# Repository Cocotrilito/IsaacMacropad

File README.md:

# IsaacMacropad
A highly versatile macropad like a "Swiss-army tool" for my computer workflow usable in many different situations such as video editing, 3d modeling, and general system control The macropad will inclide 3x3 or 2x2 key layout and at least one rotary encoder for precise control. This is my first hardware project, and im really exited about it.

## Project Overview (HackPad)

## Schematic

## PCB Design

## Case Design

## Bom 
| Item | Component | Quantity | Notes |
|-----:|----------|----------|-------|
| 1 | Seeed Studio XIAO RP2040 | 1 | Main microcontroller |
| 2 | Mechanical switches (MX compatible) | 9 | Key switches |
| 3 | Keycaps | 9 | 1u keycaps |
| 4 | EC11 Rotary Encoder | 1 | With push button |
| 5 | OLED Display (128x64 I2C) | 1 | Status display |
| 6 | Diodes 1N4148 | 9 | For key matrix |
| 7 | PCB | 1 | Custom designed |
| 8 | Case | 1 | 3D printed |

##
Thanks for reading if you liked it leave a follow! :)

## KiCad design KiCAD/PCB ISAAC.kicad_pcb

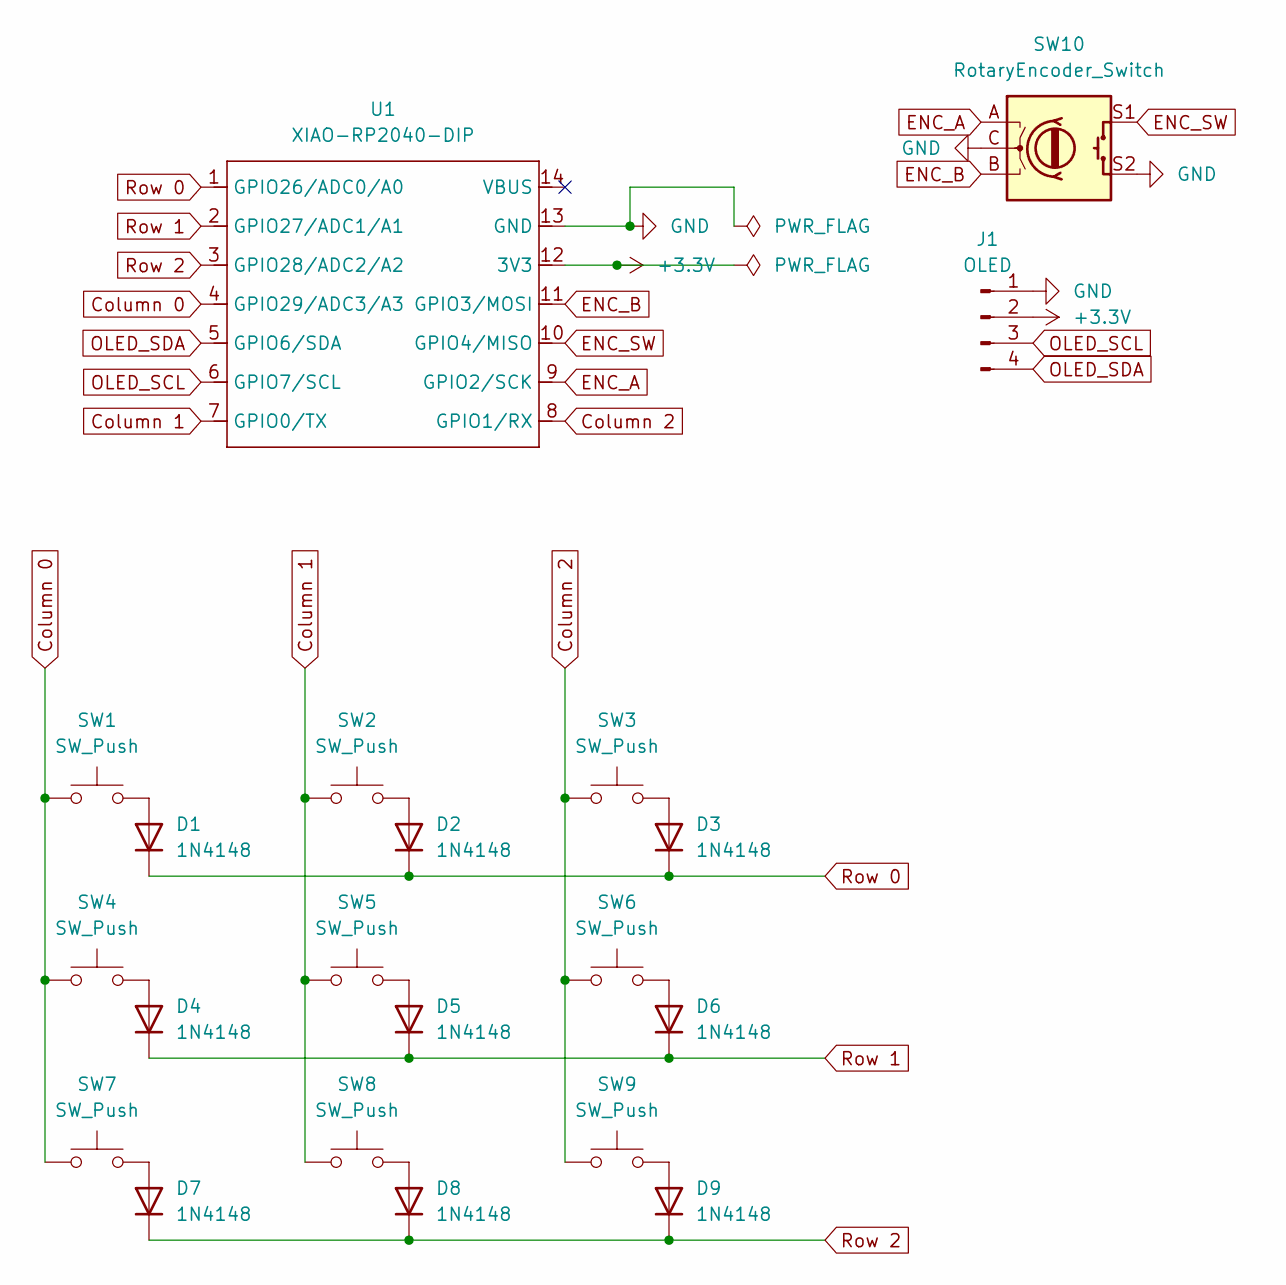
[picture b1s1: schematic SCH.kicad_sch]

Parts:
D1, D2, D3, D4, D5, D6, D7, D8, D9: 1N4148; D_DO-35_SOD27_P7.62mm_Horizontal
J1: OLED; SSD1306-0.91-OLED-4pin-128x32
SW1, SW2, SW3, SW4, SW5, SW6, SW7, SW8, SW9: SW_Push; SW_Cherry_MX_1.00u_PCB
SW10: RotaryEncoder_Switch; RotaryEncoder_Alps_EC11E-Switch_Vertical_H20mm
U1: XIAO-RP2040-DIP

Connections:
+3.3V: J1.2, U1.12 (3V3)
Column 0: SW1.1, SW4.1, SW7.1, U1.4 (GPIO29/ADC3/A3)
Column 1: SW2.1, SW5.1, SW8.1, U1.7 (GPIO0/TX)
Column 2: SW3.1, SW6.1, SW9.1, U1.8 (GPIO1/RX)
ENC_A: SW10.A, U1.9 (GPIO2/SCK)
ENC_B: SW10.B, U1.11 (GPIO3/MOSI)
ENC_SW: SW10.S1, U1.10 (GPIO4/MISO)
GND: J1.1, SW10.C, SW10.S2, U1.13 (GND)
unnamed: D1.2 (A), SW1.2
unnamed: D2.2 (A), SW2.2
unnamed: D3.2 (A), SW3.2
unnamed: D4.2 (A), SW4.2
unnamed: D5.2 (A), SW5.2
unnamed: D6.2 (A), SW6.2
unnamed: D7.2 (A), SW7.2
unnamed: D8.2 (A), SW8.2
unnamed: D9.2 (A), SW9.2
OLED_SCL: J1.3, U1.6 (GPIO7/SCL)
OLED_SDA: J1.4, U1.5 (GPIO6/SDA)
Row 0: D1.1 (K), D2.1 (K), D3.1 (K), U1.1 (GPIO26/ADC0/A0)
Row 1: D4.1 (K), D5.1 (K), D6.1 (K), U1.2 (GPIO27/ADC1/A1)
Row 2: D7.1 (K), D8.1 (K), D9.1 (K), U1.3 (GPIO28/ADC2/A2)

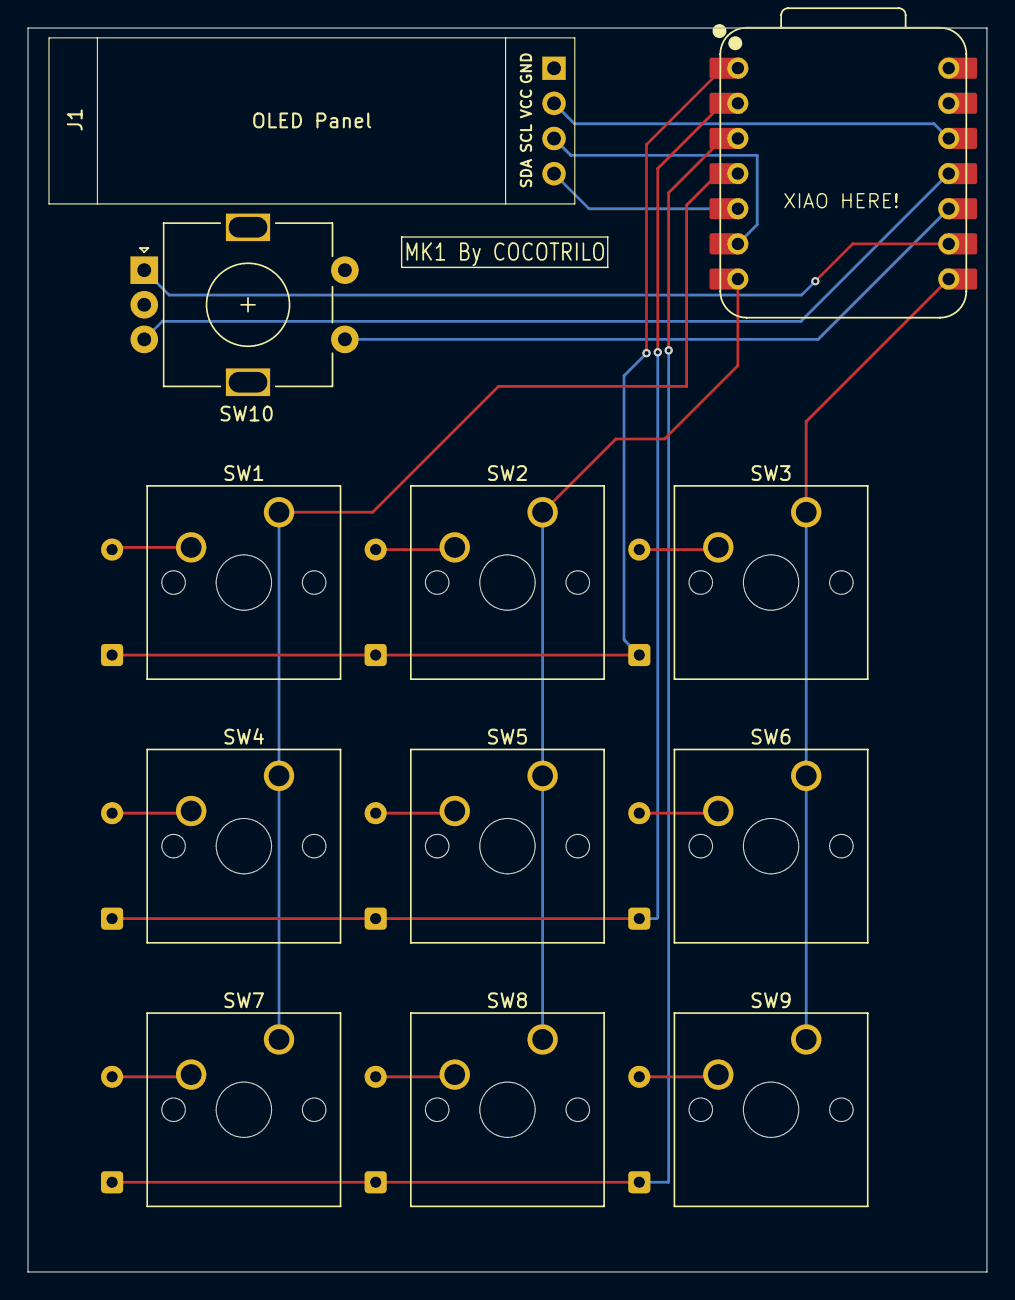
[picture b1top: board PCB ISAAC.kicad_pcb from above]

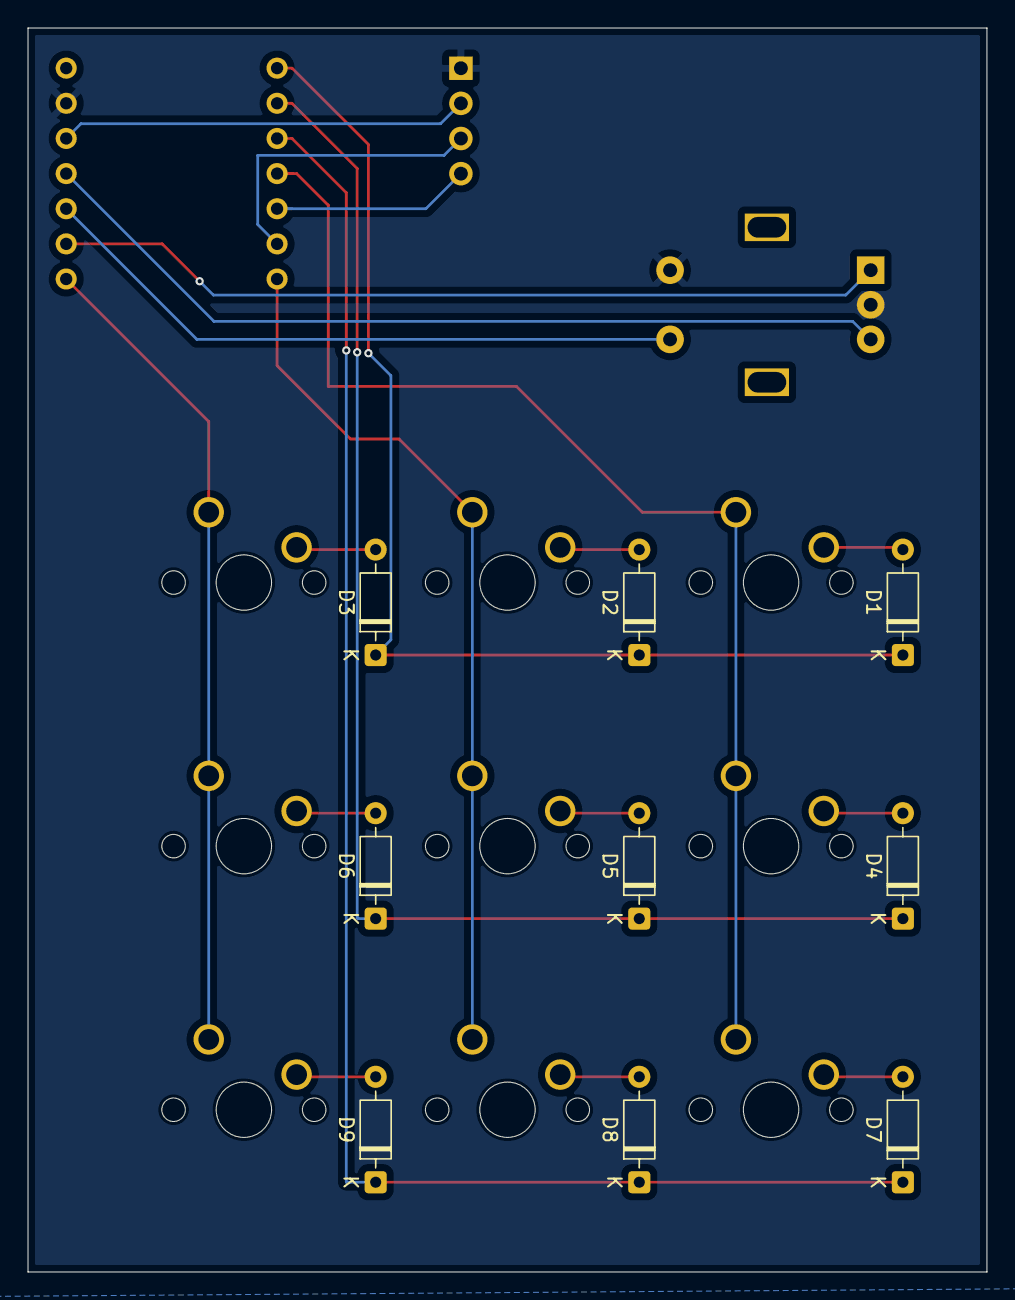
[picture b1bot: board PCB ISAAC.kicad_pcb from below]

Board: 2 copper layers, 69.3 x 89.9 mm, 21 parts (9 on the bottom side), 22 nets.

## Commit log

2026-01-04 Add CAD, KiCad, Firmware and images
